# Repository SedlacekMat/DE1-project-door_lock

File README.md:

# Door lock with a four-digit PIN, twelve button keypad, a relay and the ability to change the PIN

### Team members

Sedláček David   
Sedláček Marek   
Sedláček Matyáš    
Sladkowski David     

[Github project folder]( https://github.com/SedlacekMat/DE1-project-door_lock)

### Project objectives

Create a door lock system with a PIN (4-digit) terminal, 12 push buttons, 4-digit 7-segment display and a relay for door lock control, with the ability to change the PIN after inputting the correct value. After not getting an input for a time, the device will reset itself.

Therefore we need to be able to: 
1. assign values to button presses, keep track of the position of the currently pressed digit
2. keep time for the autoreset after an idle period and for how long should the relay stay opened
3. store the value of the correct password in a way that enables changing it
4. compare the current value with the correct value for the current digit and eventually determine if the PIN is correct or not
5. drive a common anode 4-digit 7-segment display to show what has been pressed
6. make an external circuit for the buttons, relay, LEDs and display
7. make it work on Arty A7-35T/100T

## Hardware description
### ARTY A7-100

This project is based around the FPGA board ARTY A7-100T (has better capabilites when it comes to processing compared the ARTY A7-35T, therefore being better for potential future expansions, although if budget is a concern, the current version should run on the 35T as well with no problems). It is powered by 5V, the clock frequency is 100 MHz and has 256MB of RAM (DDR3L). Out of the available pins we have used the PMOD ones, which are grouped in four connectors of twelve pins (8 signal pins, 2 VCC, and 2 ground pins). Two of these connectors are high-speed, the other two are categorized as standard. The high-speed ones were used for the displays and the standard ones for buttons and such.

### External circuit

#### Schematic

#### Used parts

#### Description

The external circuitry can be separated into three parts - the buttons, the display and the relay grouped with LEDs. 

The buttons have 3.3 V on their input, when a button is pressed, the voltage is transfered to the FPGA board input. They're connected to the supply voltage through 10k ohm resistors, this ensures that at the input of ARTY A7-100T, we can only get either a logical 1 or a logical 0, preventing undeterminable states. The 22 ohm resistors serve as protection. Each button has its own pin connection, due to the number of pins on the board being high enough for the projects needs. Potential improvement to save more pins (if the project were to be expanded input/output-wise) would be to connect them in a matrix.

For the display, the signals come in through 47 ohm resistors connected to the cathodes of the individual segments. The display used is the common anode type. The four PNP transistors are there to ensure only one display can be lit up at the same time. The anodes will be switching at periodic intervals, too fast for human vision, thus appearing as if all the diplays are lit at the same time.

As for the LEDs and the relay, the current through the red LED is limited by an 82 ohm resistor, 68 ohm for the green one. These prevent them from burning. The red LED will light up, if the PIN is incorrect, the green one in the opposite case. The relay is controlled by an NPN transistor, which, after it's base goes high, will open the relay. Connected parallel to the relay is a diode, through which the relay coil can discharge, after the relay is turned off.

Below are images of the PCB design

### PCB design

#### PCB top

#### PCB bottom

#### PCB 3D model

## VHDL modules description and simulations

### keypad_driver

#### Visual representation:

#### State diagram:

#### Description:

The keypad_driver block functions as a middleman, first translating information from the input buttons and then transferring it to the checker block. A decision was made early in the project development to discard the idea of a button matrix input in favor of working with individual buttons, seeing as the FPGA board used has enough input/output pins to do so. This also determined parts of the design of the external board, which was shown and discussed above.

The keypad_driver provides the rest of the blocks with information about keypresses, assigns 4-bit values to buttons and keeps track of the position at which the value should appear. It uses a finite state machine to cycle through 4 positions using 8 states. The reason it uses 2 states (wait for press and wait for release) for each position, is to precisely determine whether the pressed button has been released, so it can without any doubt jump to the next position. While no button is pressed, the keypad-driver sends out a 4-bit signal of “1111”, indicating to the other blocks that there is no input.

Keypad_driver also handles the automatic reset function which activates after an idle period with no input. This function has been implemented so that the lock wipes itself in the case that someone inputs, for example, two values and walks off.

From the simulation waveforms, we see that the outputted position starts correctly indexing from 0, and (although we can't see here if they are actually correct, will be seen in the other simulations) button presses change the button value output's value. We can see that two buttons at the same time are sent out as only a single number out of the two (we can count button presses by s_act, only when it's '1' is the button press legitimate), which is important for the correct function of the rest of the blocks. We also see the autoreset turning on after an idle period with no button presses, here it's arbitrary, for the simulation to be fast, the time can be changed by changing the c_DELAY_1SEC to a more realistic value.

#### Simulation waveforms:

#### testbench: [tb_keypad_driver.vhd](Individual_Modules/Testbenches/tb_keypad_driver.vhd)

#### VHDL architecture:
```vhdl
architecture Behavioral of keypad_driver is

    type decoder_state is (POS0, POS0_R, POS1, POS1_R, POS2, POS2_R, POS3, POS3_R);
    signal s_state  : decoder_state;

    signal s_cnt    : unsigned(8 - 1 downto 0);

    constant c_DELAY_1SEC : unsigned(8 - 1 downto 0) := b"1001_0110";
    constant c_ZERO       : unsigned(8 - 1 downto 0) := b"0000_0000";
    
begin
    p_decoder_fsm : process(clk)
    begin
        if rising_edge(clk) then
            if (reset = '1') then
                s_state <= POS0;
                
                num_o   <= "1111";
                act_o   <= '0';
                -- Reset counter
                s_cnt   <= c_ZERO;
                
                a_reset_o <= '0';
           
            else
                case s_state is
                
                    when POS0 =>
                        
                        pos_o <= "00";
                        
                        if (button_0 = '1') then                          
                            num_o   <= "0000";
                            s_state <= POS0_R;
                            act_o <= '1';
                            s_cnt <= c_ZERO;
                        elsif (button_1 = '1') then   
                            num_o <= "0001";
                            s_state <= POS0_R;
                            act_o <= '1';
                            s_cnt <= c_ZERO;
                        elsif (button_2 = '1') then   
                            num_o <= "0010";
                            s_state <= POS0_R;
                            act_o <= '1';
                            s_cnt <= c_ZERO;
                        elsif (button_3 = '1') then   
                            num_o <= "0011";
                            s_state <= POS0_R;
                            act_o <= '1';
                            s_cnt <= c_ZERO;    
                        elsif (button_4 = '1') then   
                            num_o <= "0100";
                            s_state <= POS0_R;
                            act_o <= '1';
                            s_cnt <= c_ZERO;        
                        elsif (button_5 = '1') then   
                            num_o <= "0101";
                            s_state <= POS0_R;
                            act_o <= '1';
                            s_cnt <= c_ZERO;       
                        elsif (button_6 = '1') then   
                            num_o <= "0110";
                            s_state <= POS0_R;
                            act_o <= '1';
                            s_cnt <= c_ZERO;         
                        elsif (button_7 = '1') then   
                            num_o <= "0111";
                            s_state <= POS0_R;
                            act_o <= '1';
                            s_cnt <= c_ZERO;         
                        elsif (button_8 = '1') then   
                            num_o <= "1000";
                            s_state <= POS0_R;
                            act_o <= '1';
                            s_cnt <= c_ZERO;         
                        elsif (button_9 = '1') then   
                            num_o <= "1001";
                            s_state <= POS0_R;
                            act_o <= '1';
                            s_cnt <= c_ZERO;         
                        --else
                 
                        end if;
                        
                    when POS0_R =>
                        
                        pos_o <= "00";
                        
                        if (button_0 = '0' and button_1 = '0' and
                            button_2 = '0' and button_3 = '0' and
                            button_4 = '0' and button_5 = '0' and
                            button_6 = '0' and button_7 = '0' and
                            button_8 = '0' and button_9 = '0') then
                            s_state <= POS1;
                            act_o <= '0';     
                        end if;
                        
                    when POS1 =>
                        
                        pos_o <= "01";
                        
                        if (button_0 = '1') then                          
                            num_o   <= "0000";
                            s_state <= POS1_R;
                            act_o <= '1';
                            s_cnt <= c_ZERO;
                        elsif (button_1 = '1') then   
                            num_o <= "0001";
                            s_state <= POS1_R;
                            act_o <= '1';
                            s_cnt <= c_ZERO;   
                        elsif (button_2 = '1') then   
                            num_o <= "0010";
                            s_state <= POS1_R;
                            act_o <= '1';
                            s_cnt <= c_ZERO;        
                        elsif (button_3 = '1') then   
                            num_o <= "0011";
                            s_state <= POS1_R;
                            act_o <= '1';
                            s_cnt <= c_ZERO;
                        elsif (button_4 = '1') then   
                            num_o <= "0100";
                            s_state <= POS1_R;
                            act_o <= '1';
                            s_cnt <= c_ZERO;       
                        elsif (button_5 = '1') then   
                            num_o <= "0101";
                            s_state <= POS1_R;
                            act_o <= '1';
                            s_cnt <= c_ZERO;          
                        elsif (button_6 = '1') then   
                            num_o <= "0110";
                            s_state <= POS1_R;
                            act_o <= '1';
                            s_cnt <= c_ZERO;          
                        elsif (button_7 = '1') then   
                            num_o <= "0111";
                            s_state <= POS1_R;
                            act_o <= '1';
                            s_cnt <= c_ZERO;  
                        elsif (button_8 = '1') then   
                            num_o <= "1000";
                            s_state <= POS1_R;
                            act_o <= '1';
                            s_cnt <= c_ZERO;       
                        elsif (button_9 = '1') then   
                            num_o <= "1001";
                            s_state <= POS1_R;
                            act_o <= '1';
                            s_cnt <= c_ZERO;        
                        else
                            if (s_cnt < c_DELAY_1SEC) then
                                s_cnt <= s_cnt + 1;
                                num_o <= "1111";
                            else
                                -- s_state <= POS0;
                                -- s_cnt <= c_ZERO;
                                a_reset_o <= '1';
                            end if;  
                        end if;
                        
                    when POS1_R =>
                        
                        pos_o <= "01";
                        
                        if (button_0 = '0' and button_1 = '0' and
                            button_2 = '0' and button_3 = '0' and
                            button_4 = '0' and button_5 = '0' and
                            button_6 = '0' and button_7 = '0' and
                            button_8 = '0' and button_9 = '0') then
                            s_state <= POS2;
                            act_o <= '0';                        
                        end if; 
                       
                    when POS2 =>
                        
                        pos_o <= "10";
                        
                        if (button_0 = '1') then                          
                            num_o   <= "0000";
                            s_state <= POS2_R;
                            act_o <= '1';
                            s_cnt <= c_ZERO;
                        elsif (button_1 = '1') then   
                            num_o <= "0001";
                            s_state <= POS2_R;
                            act_o <= '1';
                            s_cnt <= c_ZERO; 
                        elsif (button_2 = '1') then   
                            num_o <= "0010";
                            s_state <= POS2_R;
                            act_o <= '1';
                            s_cnt <= c_ZERO;      
                        elsif (button_3 = '1') then   
                            num_o <= "0011";
                            s_state <= POS2_R;
                            act_o <= '1';
                            s_cnt <= c_ZERO;         
                        elsif (button_4 = '1') then   
                            num_o <= "0100";
                            s_state <= POS2_R;
                            act_o <= '1';
                            s_cnt <= c_ZERO;        
                        elsif (button_5 = '1') then   
                            num_o <= "0101";
                            s_state <= POS2_R;
                            act_o <= '1';
                            s_cnt <= c_ZERO;         
                        elsif (button_6 = '1') then   
                            num_o <= "0110";
                            s_state <= POS2_R;
                            act_o <= '1';
                            s_cnt <= c_ZERO;        
                        elsif (button_7 = '1') then   
                            num_o <= "0111";
                            s_state <= POS2_R;
                            act_o <= '1';
                            s_cnt <= c_ZERO;       
                        elsif (button_8 = '1') then   
                            num_o <= "1000";
                            s_state <= POS2_R;
                            act_o <= '1';
                            s_cnt <= c_ZERO;         
                        elsif (button_9 = '1') then   
                            num_o <= "1001";
                            s_state <= POS2_R;
                            act_o <= '1';
                            s_cnt <= c_ZERO;         
                        else
                            if (s_cnt < c_DELAY_1SEC) then
                                s_cnt <= s_cnt + 1;
                                num_o <= "1111";
                            else
                                -- s_state <= POS0;
                                -- s_cnt <= c_ZERO;
                                a_reset_o <= '1';
                            end if;                            
                        end if;
                        
                    when POS2_R =>
                        
                        pos_o <= "10";
                        
                        if (button_0 = '0' and button_1 = '0' and
                            button_2 = '0' and button_3 = '0' and
                            button_4 = '0' and button_5 = '0' and
                            button_6 = '0' and button_7 = '0' and
                            button_8 = '0' and button_9 = '0') then
                            s_state <= POS3;
                            act_o <= '0';                      
                        end if; 
                        
                    when POS3 =>
                        
                        pos_o <= "11";
                        
                        if (button_0 = '1') then                          
                            num_o   <= "0000";
                            s_state <= POS3_R;
                            act_o <= '1';
                            s_cnt <= c_ZERO;
                        elsif (button_1 = '1') then   
                            num_o <= "0001";
                            s_state <= POS3_R;
                            act_o <= '1';
                            s_cnt <= c_ZERO;    
                        elsif (button_2 = '1') then   
                            num_o <= "0010";
                            s_state <= POS3_R;
                            act_o <= '1';
                            s_cnt <= c_ZERO;         
                        elsif (button_3 = '1') then   
                            num_o <= "0011";
                            s_state <= POS3_R;
                            act_o <= '1';
                            s_cnt <= c_ZERO;         
                        elsif (button_4 = '1') then   
                            num_o <= "0100";
                            s_state <= POS3_R;
                            act_o <= '1';
                            s_cnt <= c_ZERO;        
                        elsif (button_5 = '1') then   
                            num_o <= "0101";
                            s_state <= POS3_R;
                            act_o <= '1';
                            s_cnt <= c_ZERO;        
                        elsif (button_6 = '1') then   
                            num_o <= "0110";
                            s_state <= POS3_R;
                            act_o <= '1';
                            s_cnt <= c_ZERO;        
                        elsif (button_7 = '1') then   
                            num_o <= "0111";
                            s_state <= POS3_R;
                            act_o <= '1';
                            s_cnt <= c_ZERO;       
                        elsif (button_8 = '1') then   
                            num_o <= "1000";
                            s_state <= POS3_R;
                            act_o <= '1';
                            s_cnt <= c_ZERO;         
                        elsif (button_9 = '1') then   
                            num_o <= "1001";
                            s_state <= POS3_R;
                            act_o <= '1';
                            s_cnt <= c_ZERO;
                        else
                            if (s_cnt < c_DELAY_1SEC) then
                                s_cnt <= s_cnt + 1;
                                num_o <= "1111";
                            else
                                -- s_state <= POS0;
                                -- s_cnt <= c_ZERO;
                                a_reset_o <= '1';
                            end if;
                        end if;
                        
                    when POS3_R =>
                        
                        pos_o <= "11";
                        
                        if (button_0 = '0' and button_1 = '0' and
                            button_2 = '0' and button_3 = '0' and
                            button_4 = '0' and button_5 = '0' and
                            button_6 = '0' and button_7 = '0' and
                            button_8 = '0' and button_9 = '0' and
                            button_set = '0') then
                            s_state <= POS0;
                            act_o <= '0';          
                        end if; 
                                   
                end case;
            end if; 
        end if;
    end process p_decoder_fsm; 

end Behavioral;
``` 

### reset_driver

#### Visual representation:

#### Description:

Reset driver is a simple block, working as an OR gate for 2 input signals. Both are one-bit signals, one sent form keypad_driver as an auto-reset, the other is connected to the reset button on the external board. After any of reset_driver’s inputs is set HIGH (equal to ‘1’) it drives the output signal HIGH as well, which in this case resets all the modules connected to the output. It has been created to enable the keypad_driver to reset the whole project.

#### Simulation waveforms:

#### testbench: [tb_reset_driver.vhd](Individual_Modules/Testbenches/tb_reset_driver.vhd)

#### VHDL architecture:
```vhdl
architecture Behavioral of reset_driver is

begin
    p_reset_driver : process(m_reset, a_reset)
    begin
        
        if (a_reset = '1' or m_reset = '1') then
            reset_o <= '1';
        else
            reset_o <= '0';
        end if;
        
    end process p_reset_driver;

end Behavioral;
``` 

### demux

#### Visual representation:

#### Description:

This block is, as the name suggests, a demultiplexer. It's job is to assign the 4-bit button value input (butt_i) to one of the outputs based on the value of the 2-bit position input (pos_i). It's the first block of the two block system for the storage of the correct combination. It is always active, even when the PIN is not being changed, since there is no need to turn it off, that becomes important only on the second block of the password storage system, the 4 times 4-bit register.

In the simulation we see the behaviour exactly as described above, the input being assigned to an output based on the value of the position coming in from keypad_driver.

#### Simulation waveforms:

#### testbench: [tb_DeMux.vhd](Individual_Modules/Testbenches/tb_DeMux.vhd)

#### VHDL architecture:
```vhdl
architecture Behavioral of demux is
        begin
        
        p_demux : process(pos_i, butt_i)
        begin

            case pos_i is
                when "00" => 
                    demux0_o <= butt_i;
                when "01" => 
                    demux1_o <= butt_i;
                when "10" => 
                    demux2_o <= butt_i;
                when "11" => 
                    demux3_o <= butt_i;
                when others =>
                    demux0_o <= "1111";
                    demux1_o <= "1111";
                    demux2_o <= "1111";
                    demux3_o <= "1111";
             end case;      
        
        end process p_demux;
    end Behavioral;
``` 

### reg_4_4

#### Visual representation:

#### Description:

This block is a 16-bit register, split into four 4-bit registers. In principle, it's basically a group of D latches with a condition on the enable input. It's job is to, if the set_i (activated by a button which must be held) and pass_i (which is active ONLY when the door is unlocked by entering the correct password, for a predetermined amount of time) inputs are set high, record and store the inputs coming from the demultiplexer into the correct outputs, thus changing the combination of values that the checker block (where the comparation of the current and correct values takes place) will read. In the situation that the set_i, pass_i and reset_i inputs are all activated, the correct PIN (register output) will change to the combination "3142". The local check signal is present so that the register isn't permanently stuck in the default password branch.

In the simulation waves, we see that just the pass_i has no effect. When combined with set_i, input values start getting assigned to their corresponding output. If only set is on, nothing changes, (same for reset, not shown here, but obvious from the final project waveforms). If pass,set and reset are on, we change to the default combination.

#### Simulation waveforms:

#### testbench: [tb_Reg44.vhd](Individual_Modules/Testbenches/tb_Reg44.vhd)

#### VHDL architecture:
```vhdl

architecture Behavioral of reg_4_4 is

    signal s_local_check : std_logic;

begin

    p_register : process(pass_i, set_i, reset_i, reg0_i, reg1_i, reg2_i, reg3_i)
    begin
    
    if (pass_i='1' and set_i='1' and reset_i='1') then
            reg0_o <= "0011";
            reg1_o <= "0001";
            reg2_o <= "0100";
            reg3_o <= "0010";
            s_local_check <= '1';
    elsif (pass_i='1' and set_i='1' and reset_i='0' and s_local_check <= '0') then
            reg0_o <= reg0_i;
            reg1_o <= reg1_i;
            reg2_o <= reg2_i;
            reg3_o <= reg3_i;
    elsif (set_i = '0') then -- pass_i='1' and
        s_local_check <= '0';
    end if;
    
    end process p_register;
end Behavioral;
``` 

### checker

#### Visual representation:

#### Description:

The checker block is an amalgamation of two separate blocks, pass_check (the Moore FSM for judging the entered combination) and the timer block.

The simulation waveform will be described for each block separately, the screenshot below can be referred to later for verification.

#### Simulation waveforms:

#### testbench: [tb_checker.vhd](Individual_Modules/Testbenches/tb_checker.vhd)

#### VHDL architecture:
```vhdl
architecture Behavioral of checker is

    signal s_timestart  : std_logic;
    signal s_seconds    : std_logic_vector(2 downto 0);

begin

    timer0 : entity work.timer
    
        generic map(
            g_MAXCHECK => 50 -- realistically 100 000 000
        )
        port map(
            clk => clk,
            reset_i => reset_i,
            timestart_i => s_timestart,
            seconds_o => s_seconds 
        );
        
    pass_check0 :  entity work.pass_check
          port map(
                butt_i       =>  butt_i,
                reset_i      =>  reset_i,
                write_i      =>  write_i,
                seconds_i    =>  s_seconds,
                ledg_o       =>  ledg_o,
                ledr_o       =>  ledr_o,
                relayint_o   =>  relayint_o,
                relayext_o   =>  relayext_o,
                timestart_o  =>  s_timestart,
                check0_i     =>  check0_i,
                check1_i     =>  check1_i,
                check2_i     =>  check2_i,
                check3_i     =>  check3_i,
                check0_o     =>  check0_o,
                check1_o     =>  check1_o,
                check2_o     =>  check2_o,
                check3_o     =>  check3_o
                                
                );  

end Behavioral;
``` 

### pass_check

#### State diagram:

#### Description:

As stated, this is a Moore type finite state machine, meaning that the outputs are determined by the current state. As we can see from the diagram, we have an initial NEUTRAL state, where all the outputs are off and the combination being sent to the displays is "1111", which the diplay driver interprets as "nothing lights up". When a button is pressed, it's value comes through the butt_i input and the write_i input activates, that way, we ensure we process only legitimate button presses and enables us to read the same value pressed twice as two separate inputs.

When we detect a legitimate button press, we compare the value at butt_i to the value of the passwords first number (check0_i), if they match, the state changes to PASS0, if they don't, we go to FAIL0 and so on. This means, each button press is compared separately. Two things to note are: Firstly, that we can slip into a fail state at each separate button press and not know about it until we enter the whole combination. All inputs are outputted to the display no matter if they are correct or not. Secondly, if the reset_i is activated at any time (either manually or automatically by keypad_driver), we are returned back to the NEUTRAL state. This is NOT incorporated into the state diagram, since it quickly becomes overcrowded by lines and conditions and results mostly in confusion, which defeats the purpose of making a state diagram in the first place.

We see the diagram has two branches, at the end of each there is a final state, either FAIL_FINAL or PASS_FINAL. FAIL_FINAL results in the red LED turning on and it sends a signal through the timestart_o output to the timer, which starts counting one "tick" of time (in the real implementation seconds, had to be shortened in the simulation). When the correct number of ticks is read on the seconds_i input, the state shifts to the NEUTRAL state. Similarly to this the PASS_FINAL state activates the green LED and opens the relay for five time "ticks" (time is kept by the same mechanism as above). During this, it also send an internal signal through the relayint_o output to the reg_4_4 register, which allows the user to change the correct combination for the duration of these five "ticks". After those pass, pass_check shifts to the NEUTRAL state. If we change the combination to the default one by pressing set and reset, it shifts to NEUTRAL immediately.

There is potential for future improvement here, namely that the relayint_o could stay on indefinetly, as long as set is pressed during the time that relayint_o was 
already turned on by the door opening.

From the simulation waveforms we see that the finite state machine is working as intended (described above), outputted values for the display are in the correct position, LEDs, relay and timestart turn on appropriately, and in NEUTRAL all outputs go to "1111". Note that the FINAL states are not timed since this is only the pass_check block.

#### Simulation waveforms:

#### testbench: [tb_passCheck.vhd](Individual_Modules/Testbenches/tb_passCheck.vhd)

#### VHDL architecture:
```vhdl
architecture Behavioral of pass_check is
    type t_state is (NEUTRAL,
                     PASS0,
                     PASS1,
                     PASS2,
                     PASS_FINAL,
                     FAIL0,
                     FAIL1,
                     FAIL2,
                     FAIL_FINAL);
    
    signal s_state  : t_state;

begin
    
    p_passcheck: process(reset_i, write_i, butt_i,seconds_i, check0_i, check1_i, check2_i, check3_i)
    begin
        if (reset_i ='1') then
            s_state <= NEUTRAL;
        elsif (reset_i ='0') then
            case s_state is 
                
                when NEUTRAL =>
                
                    timestart_o <= '0';
                    ledg_o <= '0';
                    ledr_o <= '0';
                    relayint_o <= '0';
                    relayext_o <= '0';
                
                    check0_o <= "1111";
                    check1_o <= "1111";
                    check2_o <= "1111";
                    check3_o <= "1111";
                    if ((check0_i = butt_i) and write_i = '1') then
                        check0_o <= butt_i;
                        s_state <= PASS0;
                    elsif ((check0_i /= butt_i) and write_i = '1') then
                        check0_o <= butt_i;
                        s_state <= FAIL0;
                    else
                        null;
                    end if;
                    
                when PASS0 =>
                    if ((check1_i = butt_i) and write_i = '1') then
                        check1_o <= butt_i;
                        s_state <= PASS1;
                    elsif ((check1_i /= butt_i) and write_i = '1') then
                        check1_o <= butt_i;
                        s_state <= FAIL1;
                    else
                        null;
                    end if;
                
                when PASS1 =>
                    if ((check2_i = butt_i) and write_i = '1') then
                        check2_o <= butt_i;
                        s_state <= PASS2;
                    elsif ((check2_i /= butt_i) and write_i = '1') then
                        check2_o <= butt_i;
                        s_state <= FAIL2;
                    else
                        null;
                    end if;
                
                when PASS2 =>
                    if ((check3_i = butt_i) and write_i = '1') then
                        check3_o <= butt_i;
                        s_state <= PASS_FINAL;
                    elsif ((check3_i /= butt_i) and write_i = '1') then
                        check3_o <= butt_i;
                        s_state <= FAIL_FINAL;
                    else
                        null;
                    end if;
                    
                when PASS_FINAL =>
                    timestart_o <= '1';
                    if (seconds_i < "101") then
                        ledg_o <= '1';
                        relayint_o <= '1';
                        relayext_o <= '1';
                    elsif (seconds_i = "101") then
                        ledg_o <= '0';
                        relayint_o <= '0';    
                        relayext_o <= '0';                       
                        timestart_o <= '0';
                        s_state <= NEUTRAL;
                    end if;
                
                when FAIL0 =>
                    if (write_i = '1') then
                        check1_o <= butt_i;
                        s_state <= FAIL1;
                    end if;    
                
                when FAIL1 =>
                    if (write_i = '1') then
                        check2_o <= butt_i;
                        s_state <= FAIL2;
                    end if;
                    
                when FAIL2 =>
                    if (write_i = '1') then
                        check3_o <= butt_i;
                        s_state <= FAIL_FINAL;
                    end if;
                
                when FAIL_FINAL =>
                    timestart_o <= '1';
                    if (seconds_i < "001") then
                        ledr_o <= '1';
                        relayint_o <= '0'; 
                        relayext_o <= '0'; 
                    elsif (seconds_i = "001") then
                        ledr_o <= '0';                        
                        timestart_o <= '0';
                        s_state <= NEUTRAL;
                    end if;
                    
                when others =>
                    s_state <= NEUTRAL;
                    
              end case;
             end if;
           end process p_passcheck;     
                  
end Behavioral;
``` 

### timer

#### Description:

As soon as timestart_i activates, this block starts counting clock pulses. There are two counters, one is, as mentioned, for individual clock pulses, the other is for counting how many times has the previous counter filled (determined by a constant), thus counting the time "ticks" that have passed. The second counter is outputted to seconds_o, which is read by pass_check, once it reads the correct number from its seconds_i, it shifts to NEUTRAL, in which, timestart_o is deactivated. This effectively resets the timer and it stops counting clock pulses.

In the simulation waveforms, we see that once timestart activates, we start counting clock periods locally, and each set number of periods, the seconds output changes its values up by one until the timestart input goes to zero. Here we count higher than 101 since nothing is stopping the timer, because timestart is controlled by pass_check.

#### Simulation waveforms:

#### testbench: [tb_timer.vhd](Individual_Modules/Testbenches/tb_timer.vhd)

#### VHDL architecture:
```vhdl
architecture Behavioral of timer is
        signal s_cnt_local : natural:= 0;
        signal s_seconds_local : natural:= 1;
begin

p_timer: process(clk)
      begin 
        if timestart_i = '1' then
          if rising_edge(clk) then
              if  (reset_i = '1') then
                    s_cnt_local <= 0;
                    seconds_o <= "000";
              elsif (s_cnt_local >= (g_MAXCHECK - 1)) then
                  s_cnt_local <= 0;                
                  s_seconds_local <= (s_seconds_local + 1);
                  seconds_o <= std_logic_vector(TO_UNSIGNED(s_seconds_local,3)); 
              else
                  s_cnt_local <= (s_cnt_local + 1);
              end if;
          end if;
          elsif timestart_i = '0' then
          seconds_o <= "000"; 
          s_seconds_local <= 1;
          s_cnt_local <= 0;
        end if;
                           
      end process p_timer;  

end Behavioral;
``` 

### driver_7seg_4digits

#### Visual representation:

#### Description:

This block and its parts serve, as the name implies, as a driver for the four digit seven segment display used to display the typed in combination, receiving the outputs from the checker block. It was almost entirely pre-made (created during the semester in computer excersises) and only very slightly modified for the specific needs of this project, in the case of hex7seg and the p_mux process. The two main functions of the driver are: one, it connects all the sub-blocks together, two, it hosts the multiplexer process, that is needed to drive multi-digit seven segment displays, switching between the displays at a constant interval, too fast for human perception (here it's 4ms per display, shortened for simulation). The output for the decimal point was removed after some deliberation, originally there was an idea to use the decimal point as an indicator that the wrong combination has been entered, but it was foregone in the favor of having an external LED serve this purpose, driven by the checker block. 

From the simulation waveforms, we can see that the input numbers are being diplayed correctly and the anode is being changed in the desired order, so that the displays show the values from left to right.

#### Simulation waveforms:

#### testbench: [tb_driver_7seg_4digits.vhd](Individual_Modules/Testbenches/tb_driver_7seg_4digits.vhd)

#### VHDL architecture:
```vhdl
architecture Behavioral of driver_7seg_4digits is

    -- Internal clock enable
    signal s_en  : std_logic;
    -- Internal 2-bit counter for multiplexing 4 digits
    signal s_cnt : std_logic_vector(2 - 1 downto 0);
    -- Internal 4-bit value for 7-segment decoder
    signal s_hex : std_logic_vector(4 - 1 downto 0);

begin
    --------------------------------------------------------------------
    -- Instance (copy) of clock_enable entity generates an enable pulse
    -- every 4 ms
    clk_en0 : entity work.clock_enable
        generic map(
            g_MAX => 4 -- realistically 400 000   
        )
        port map(
            clk   =>  clk,
            reset =>  reset,
            ce_o  =>  s_en
        );

    --------------------------------------------------------------------
    -- Instance (copy) of cnt_up_down entity performs a 2-bit down
    -- counter
    bin_cnt0 : entity work.cnt_up_down
        generic map(
            g_CNT_WIDTH => 2
        )
        port map(
            clk       => clk,
            reset     => reset,
            en_i      => s_en,
            cnt_up_i  => '0',
            cnt_o     => s_cnt
        );

    --------------------------------------------------------------------
    -- Instance (copy) of hex_7seg entity performs a 7-segment display
    -- decoder
    hex2seg : entity work.hex_7seg
        port map(
            hex_i => s_hex,
            seg_o => seg_o
        );

    --------------------------------------------------------------------
    -- p_mux:
    -- A combinational process that implements a multiplexer for
    -- selecting data for a single digit, a decimal point signal, and 
    -- switches the common anodes of each display.
    --------------------------------------------------------------------
    p_mux : process(s_cnt, data0_i, data1_i, data2_i, data3_i)
    begin
        case s_cnt is
            when "11" =>
                s_hex <= data0_i;
                dig_o <= "0111";

            when "10" =>
                s_hex <= data1_i;
                dig_o <= "1011";

            when "01" =>
                s_hex <= data2_i;
                dig_o <= "1101";

            when others =>
                s_hex <= data3_i;
                dig_o <= "1110";

        end case;
    end process p_mux;

end architecture Behavioral;
``` 

### clock_enable (not simulated seperately, was simulated during computer excersises)

#### Description:

This is a clock divider, similar to what is used in the timer block, it counts up to a predefined (g_MAX) number of clock pulses, and toggles it's output accordingly, to create a slower clock, that drives the other blocks in the display driver. It has a synchronous reset, since the condition for it is only checked after determining a rising edge clock event.

### cnt_up_down (not simulated seperately, was simulated during computer excersises)

#### Description:

A counter used by the multiplexer process to determine which input it is supposed to connect to the output. Since this is a four digit number, it counts from 0 to 3, then wraps around. It's also able to change between counting up and down, thus the name, but we do not use this feature in the project.

### hex7seg (not simulated seperately, was simulated during computer excersises)

#### Description:

This block assigns a value to the output of the multiplexer process, assigning seven-bit output values to the four-bit input ones, controlling each segment. It is set up to control a common anode display (lights up on '0'). A small modification was needed here, since "1111" is used as a value to communicate that nothing is lit up on the display, so its assigned output was changed to "1111111" 

## TOP module description and simulations

### door_lock

#### Visual representation:

#### Description:

This is the block that houses all interconnecting internal signals for the entire project. It has been made separate from the top block, so that the project's code isn't entirely dependent on the used Arty A7-100T and a potential change of the FPGA board is easier to implement, e.g. top is effectively seperate from the functional code. In the simulation screenshots below we can see the entire project working (simulations are split for value readability). 

In the first one we can see: First, a situation where two buttons are pressed at the same time. We can see it chooses one of them at random, and proceeds as if only one button was pressed, which is the wanted result, as was already mentioned in the keypad_driver section. Then there is the manual reset being tested, we see the that the display wipes itself and the lock returns to the initial neutral state as wanted. The last thing tested is the autoreset, two buttons (wrong combination, doesn't really matter in this case) have been pressed, then, after an idle period with no input, the autoreset signal (internal, not shown, effects observable) is triggered, wiping the display and sending the lock to NEUTRAL, which is the expected result.

In the second one: First, a correct combination is entered ("3142", the default), which changes the locks state from NEUTRAL to PASS0, PASS1, PASS2 and then PASS_FINAL, which opens the relay, lights up the green LED and sends a signal to the timer which starts counting as we can see. When the door is opened, set is pressed and held and a new password is entered ("1234"), rewriting the values stored in the register block (we can see checker inputs connected to these). When the timer reaches five "ticks" it sends the lock to NEUTRAL, turning off the relay, LED and wiping the display and timer. After a while, "1234" is entered, the lock again step by step enters the PASS_FINAL state. Then, when the door is opened, set is held and reset is pressed, the correct combination changes to the default "3142" and immediately without waiting for the timer to finish sets the state to NEUTRAL, except for the display, relay and LED, which wipes/ turns off when reset is released. This could be problematic, since this way, after entering the correct PIN and holding set and reset while the door is opened, it can be held open indefinetly, as long as reset is being held down. A potential problem to be fixed in a future version, but since it requires the knowledge of the password in the first place, it's not that major of an issue. The last thing checked is the ability to enter the same number twice, which we see works, but since the combination is wrong (even though three out of four values are correct, showing that the order of the entered numbers matters), we go through the FAIL states up to FAIL_FINAL, where we see the red LED light up, timer start up, lasting in this state for one "tick" and then returning to NEUTRAL.

Thus, we see the lock fulfills the project goals set at the start, and as far as we have been able to find, has no major issues, although a small number of minor ones are still present at this time (both with the set password feature), mentioned above, namely that the interval for which the password can be changed is fixed (it is desirable to extend it by holding down the set button) and then the fact that after a set+reset password change, holding reset keeps the door open indefinetly.

#### Simulation waveforms:

#### testbench (both in one file): [tb_door_lock.vhd](Final_Project/Testbench/tb_door_lock.vhd)

#### VHDL architecture:
```vhdl
architecture Behavioral of door_lock is

    signal s_num  : STD_LOGIC_VECTOR (4 - 1 downto 0);
    signal s_pos  : STD_LOGIC_VECTOR (2 - 1 downto 0);
    signal s_act  : STD_LOGIC;
    
    signal s_reset_o : STD_LOGIC;
    signal s_a_reset : STD_LOGIC;
    
    signal s_reg0  : STD_LOGIC_VECTOR (4 - 1 downto 0);
    signal s_reg1  : STD_LOGIC_VECTOR (4 - 1 downto 0);
    signal s_reg2  : STD_LOGIC_VECTOR (4 - 1 downto 0);
    signal s_reg3  : STD_LOGIC_VECTOR (4 - 1 downto 0);
    
    signal s_check0  : STD_LOGIC_VECTOR (4 - 1 downto 0);
    signal s_check1  : STD_LOGIC_VECTOR (4 - 1 downto 0);
    signal s_check2  : STD_LOGIC_VECTOR (4 - 1 downto 0);
    signal s_check3  : STD_LOGIC_VECTOR (4 - 1 downto 0);
    
    signal s_driver0  : STD_LOGIC_VECTOR (4 - 1 downto 0);
    signal s_driver1  : STD_LOGIC_VECTOR (4 - 1 downto 0);
    signal s_driver2  : STD_LOGIC_VECTOR (4 - 1 downto 0);
    signal s_driver3  : STD_LOGIC_VECTOR (4 - 1 downto 0);
    
    signal s_relay  : STD_LOGIC;

begin

    keypad_driver0  : entity work.keypad_driver
        port map(
            clk         => clk,  
            reset       => s_reset_o,
        
            button_set  => set,
            button_0    => button_0,
            button_1    => button_1,
            button_2    => button_2,
            button_3    => button_3,
            button_4    => button_4,
            button_5    => button_5,
            button_6    => button_6,
            button_7    => button_7,
            button_8    => button_8,
            button_9    => button_9,
                    
            a_reset_o   => s_a_reset,        
            act_o       => s_act,
            pos_o       => s_pos,
            num_o       => s_num
        );
        
    reset_driver0   : entity work.reset_driver
        port map(
            m_reset     => m_reset,
            a_reset     => s_a_reset,
            
            reset_o     => s_reset_o   
        );
        
    demux0  : entity work.demux
        port map(
            butt_i      => s_num,
            pos_i       => s_pos,
            
            demux0_o    => s_reg0,
            demux1_o    => s_reg1,
            demux2_o    => s_reg2,
            demux3_o    => s_reg3
        );
        
    reg_4_40  : entity work.reg_4_4
        port map(
            set_i       => set,
            pass_i      => s_relay,
            reset_i     => s_reset_o,
            reg0_i      => s_reg0,
            reg1_i      => s_reg1,
            reg2_i      => s_reg2,
            reg3_i      => s_reg3,
            
            reg0_o      => s_check0,
            reg1_o      => s_check1,
            reg2_o      => s_check2,
            reg3_o      => s_check3
        );
        
    checker0  : entity work.checker
        port map(
            clk         => clk,
            butt_i      => s_num,
            reset_i     => s_reset_o,
            write_i     => s_act,
            
            ledg_o      => ledg_o,
            ledr_o      => ledr_o,
            
            relayext_o  => relayext_o,
            relayint_o  => s_relay,
            check0_i    => s_check0,
            check1_i    => s_check1,
            check2_i    => s_check2,
            check3_i    => s_check3,
            
            check0_o    => s_driver0,
            check1_o    => s_driver1,
            check2_o    => s_driver2,
            check3_o    => s_driver3
        );
       
    driver_7seg_4digits0 : entity work.driver_7seg_4digits
        port map(
            clk          => clk,
            reset        => s_reset_o,
            
            data0_i      => s_driver0,
            data1_i      => s_driver1,
            data2_i      => s_driver2,
            data3_i      => s_driver3,
            
            dig_o        => dig_o,
            seg_o        => seg_o
        );

end Behavioral;
``` 

### TOP

#### Visual representation:

#### Description:

Provides interface between the project's (door_lock's) code and the pins of the FPGA. The chosen pins can be seen in the diagram above or the VHDL code below.

#### Constraints: [Arty-A7-100T.xdc](Final_Project/Constraints/Arty-A7-100T.xdc)
#### Bitstream file: [top.bit](Project_Files/Bitstream/top.bit)

#### VHDL architecture:
```vhdl
architecture Behavioral of top is

begin
    door_lock : entity work.door_lock
        port map(
            clk         => CLK100MHZ,
            -------------------------
            button_0    => B0,
            button_1    => B1,
            button_2    => B2,
            button_3    => B3,
            button_4    => B4,
            button_5    => B5,
            button_6    => B6,
            button_7    => B7,
            button_8    => B8,
            button_9    => B9,
            set         => B_SET,
            m_reset     => B_RESET,
            -------------------------
            ledg_o      => LED_G,
            ledr_o      => LED_R,
            relayext_o  => RELAY_EXT,
            seg_o       => CA, 
            dig_o       => AN  
        );

end Behavioral;
```
### Project Files: [door_lock.zip](Project_Files/door_lock.zip)

## Video

[Video na YouTube](https://www.youtube.com/watch?v=wTUz-jFWRrE)

## References

   1. https://github.com/tomas-fryza/Digital-electronics-1
   2. https://www.youtube.com/channel/UCbUe5SLMSZlSzCuJP81lU0A and https://www.youtube.com/c/iit/videos
   3. https://forums.xilinx.com/

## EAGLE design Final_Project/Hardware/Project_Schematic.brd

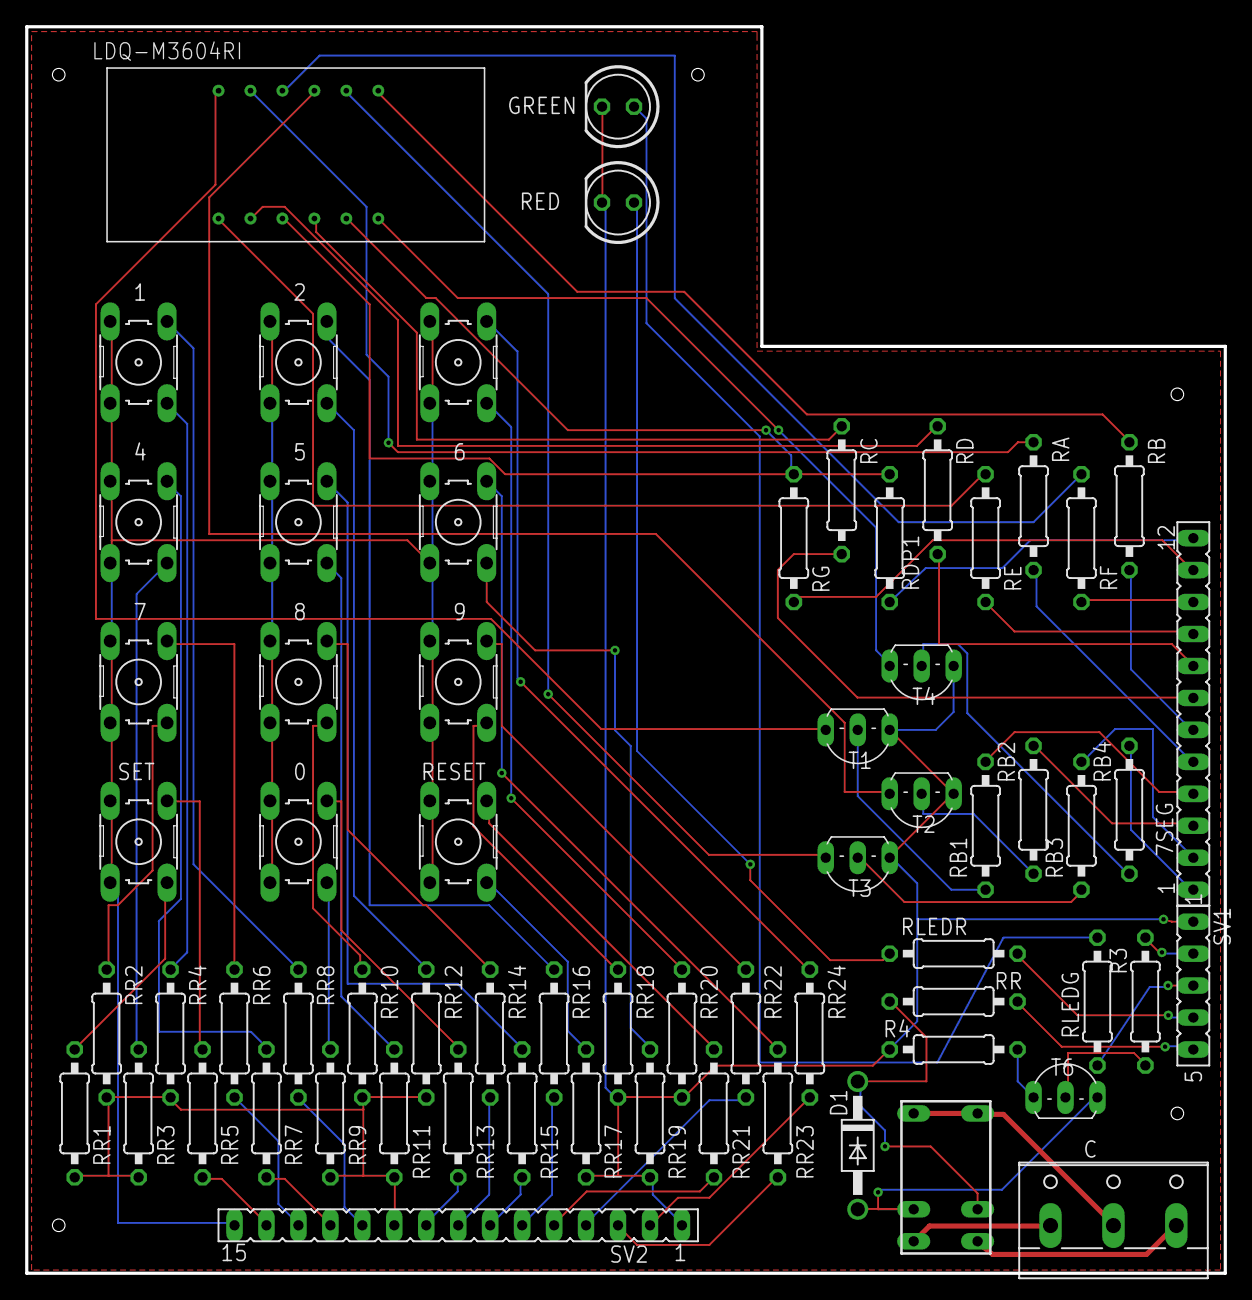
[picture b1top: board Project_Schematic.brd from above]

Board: 2 copper layers, 95.2 x 99.1 mm, 67 parts (0 on the bottom side), 77 nets.

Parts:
0, 1, 2, 3, 4, 5, 6, 7, 8, 9: B3F-10XX
7SEG: FE12
C: W237-103
D1: 1N4004; DO41-10
GREEN: LED5MM
K2: G5V1
LDQ-M3604RI: 4X7SEGMENTDISPLAY.; 4X7SCHEM
R3: 12k; 0207/10
R4: 10; 0207/10
RA: 47; 0207/10
RB: 47; 0207/10
RB1, RB2, RB3, RB4: 3k9; 0207/10
RC: 47; 0207/10
RD: 47; 0207/10
RDP1: 47; 0207/10
RE: 47; 0207/10
RED: LED5MM
RESET: B3F-10XX
RF: 47; 0207/10
RG: 47; 0207/10
RLEDG: 68; 0207/10
RLEDR: 82; 0207/10
RR: 10; 0207/10
RR1, RR2, RR3, RR4, RR9, RR10, RR11, RR12, RR17, RR18, RR19, RR20: 10k; 0207/10
RR5, RR6, RR7, RR8, RR13, RR14, RR15, RR16, RR21, RR22, RR23, RR24: 22; 0207/10
SET: B3F-10XX
SV1: FE05-1
SV2: FE15
T1, T2, T3, T4: 2N3906; TO92-EBC
T6: 2N3903; TO92-EBC

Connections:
A11-7: RR7.2, SV2.12
A18-8: RR15.2, SV2.7
B18-5: RR14.2, SV2.8
C15-E: 7SEG.9, RE.2
D3-6: RR22.2, SV2.4
D4-3: RR21.2, SV2.5
D12-SET: RR8.2, SV2.11
D13-2: RR13.2, SV2.9
D15-F: 7SEG.10, RF.2
E2-RESET: RR24.2, SV2.2
E15-DP1: 7SEG.12, RDP1.1
E16-G: 7SEG.11, RG.2
F4-9: RR23.2, SV2.3
GND: GREEN.K, R4.2, RED.K, RR17.2, RR18.2, RR19.2, RR20.2, SV1.1, SV2.1, T1.E, T2.E, T3.E, T4.E
J15-A: 7SEG.5, RA.2
J17-D: 7SEG.8, RD.2
K15-B: 7SEG.6, RB.2
K16-0: RR16.2, SV2.6
unnamed: RB1.1, T1.B
unnamed: LDQ-M3604RI.DIG2, T2.C
unnamed: LDQ-M3604RI.DIG1, T1.C
unnamed: LDQ-M3604RI.DIG3, T3.C
unnamed: LDQ-M3604RI.DIG4, T4.C
unnamed: RB2.1, T2.B
unnamed: RB3.1, T3.B
unnamed: RB4.1, T4.B
unnamed: RR1.2, RR2.2, RR3.2, RR4.2, RR9.2, RR10.2, RR11.2, RR12.2, SV2.10
unnamed: LDQ-M3604RI.A, RA.1
unnamed: LDQ-M3604RI.B, RB.1
unnamed: LDQ-M3604RI.C, RC.1
unnamed: LDQ-M3604RI.D, RD.1
unnamed: LDQ-M3604RI.E, RE.1
unnamed: LDQ-M3604RI.F, RF.1
unnamed: LDQ-M3604RI.G, RG.1
unnamed: LDQ-M3604RI.DP1, RDP1.2
unnamed: RR5.1, SET.1
unnamed: 7.1, RR6.1
unnamed: RR5.2, SV2.14
unnamed: 1.1, RR8.1
unnamed: D1.C, K2.2, RR.2
unnamed: 0.1, RR13.1
unnamed: 8.1, RR14.1
unnamed: 2.1, RR16.1
unnamed: 8.2, RR10.1
unnamed: 5.2, RR11.1
unnamed: R3.1, T6.B
unnamed: R4.1, T6.E
unnamed: 2.2, RR12.1
unnamed: 0.2, RR9.1
unnamed: 5.1, RR15.1
unnamed: GREEN.A, RLEDG.2
unnamed: RED.A, RLEDR.1
unnamed: RR1.1, SET.2
unnamed: 7.2, RR2.1
unnamed: 4.2, RR3.1
unnamed: 1.2, RR4.1
unnamed: 4.1, RR7.1
unnamed: K2.9, T6.C
unnamed: RR6.2, SV2.13
unnamed: 0.3, 0.4, 2.3, 2.4, 5.3, 5.4, 8.3, 8.4
unnamed: RESET.1, RR21.1
unnamed: 9.1, RR22.1
unnamed: 3.1, RR24.1
unnamed: 9.2, RR18.1
unnamed: 6.2, RR19.1
unnamed: 3.2, RR20.1
unnamed: RESET.2, RR17.1
unnamed: 6.1, RR23.1
unnamed: 1.3, 1.4, 3.3, 3.4, 4.3, 4.4, 6.3, 6.4, 7.3, 7.4, 9.3, 9.4, RESET.3, RESET.4, SET.3, SET.4, SV2.15
T13-RELAY: R3.2, SV1.2
U12-DIG1: 7SEG.4, RB1.2
U14-LEDR: RLEDR.2, SV1.4
V10-DIG3: 7SEG.2, RB3.2
V11-DIG4: 7SEG.1, RB4.2
V12-DIG2: 7SEG.3, RB2.2
V14-LEDG: RLEDG.1, SV1.3
VCC: RR.1, SV1.5
